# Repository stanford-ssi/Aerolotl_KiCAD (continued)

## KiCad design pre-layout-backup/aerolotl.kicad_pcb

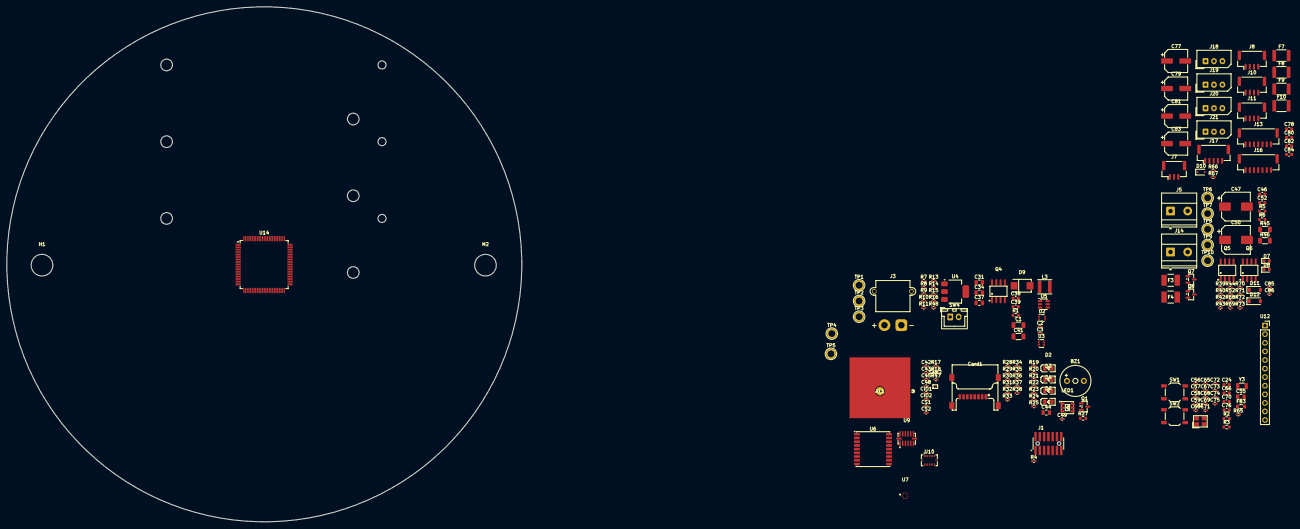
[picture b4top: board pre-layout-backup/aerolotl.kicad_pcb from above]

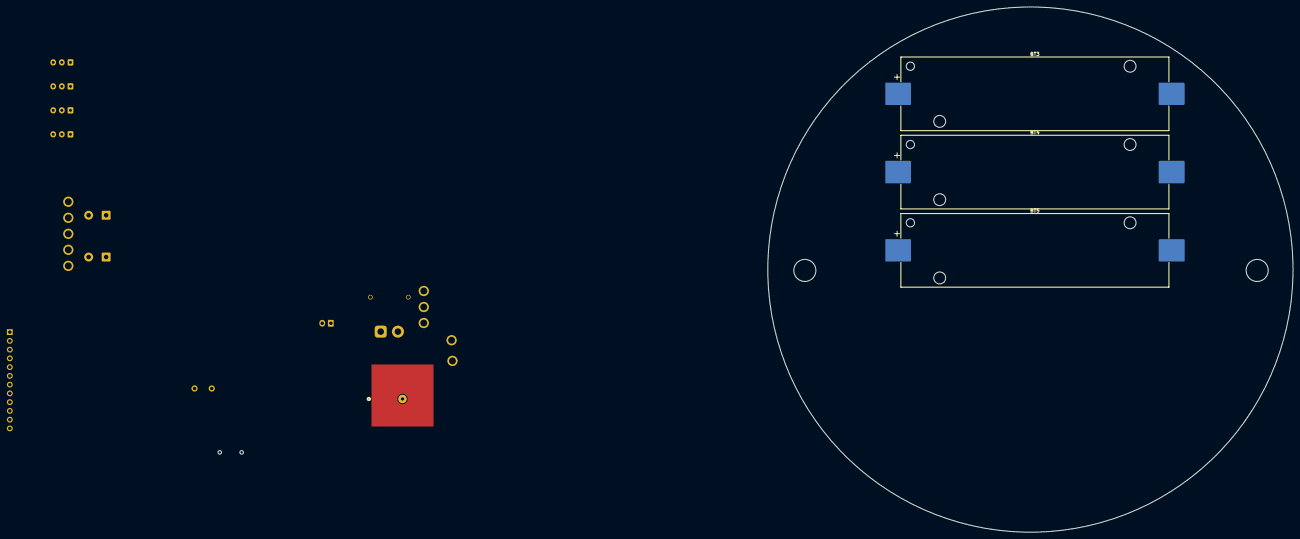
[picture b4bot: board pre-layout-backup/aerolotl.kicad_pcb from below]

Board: 4 copper layers, 152.4 x 152.4 mm, 181 parts (3 on the bottom side), 129 nets, no tracks yet.

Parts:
AE1: GP.1575.18.4.A.02; ANT_GP.1575.18.4.A.02_TAL
BT3, BT4, BT5: Battery_Cell; BatteryHolder_Keystone_1042_1x18650
BZ1: HNB09A03; BUZ-TH_BD9.0-P5.00-D0.6-FD
C1, C41: 100u; C_1206_3216Metric
C2, C3: 1u; C_0402_1005Metric
C24, C38, C39: 100n; C_0603_1608Metric
C31, C34, C44: 22u; C_0805_2012Metric
C37: 4u7; C_0805_2012Metric
C42, C43, C45, C48: 100nF; C_0402_1005Metric
C46, C52: 150n; C_0603_1608Metric
C47, C50: 330u; CP_Elec_8x10
C49, C56, C57, C58, C59, C60, C65, C69, C75, C85, C86: 100n; C_0402_1005Metric
C55: 4.7u; C_0805_2012Metric
C66, C70, C76: 1u; C_0603_1608Metric
C67, C68: 2u2; C_0402_1005Metric
C71, C72, C73, C74: 15p; C_0402_1005Metric
C77, C79, C81, C83: 100u 25V; CP_Elec_6.3x7.7
C78, C80, C82, C84: 100n 50V; C_0603_1608Metric
CIO1: 1u; C_0402_1005Metric
CIO2: 100n; C_0402_1005Metric
CS1: 100n; C_0402_1005Metric
CS2: 1u; C_0402_1005Metric
Card1: TF-102-15_SD_read; TF-SMD_TF-102-15
D2: STM LED; LED0805-R-RD
D3: 3V3 LED; LED0805-R-RD
D4: USB LED; LED0805-R-RD
D6: ARM LED; LED0805-R-RD
D7, D8: LED; LED_0603_1608Metric
D9: SMBJ15A; SMB_L4.6-W3.6-LS5.3-RD
D10: PESD5V0S1BA; D_SOD-323
D11, D12: 1N4148W; D_SOD-123
F3, F4: 1812L150/24MR; FUSE_1812L150&slash_24_LTF
F7, F8, F9, F10: 1812L300/24SLER; Fuse_1812_4532Metric
FB3: 100; L_0805_2012Metric
H1, H2: MountingHole; MountingHole_6.4mm_M6_ISO7380
J1: FTSH-107-STDC14; STDC14_SAMTEC_FTSH-107-01-L-DV-K-A
J3: Pin Switch Conn; AMASS_XT30PW-M_1x02_P2.50mm_Horizontal
J5, J14: Screw_Terminal_01x02; TerminalBlock_Phoenix_MKDS-1,5-2-5.08_1x02_P5.08mm_Horizont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
J7: SPARE_ADC1; JST_GH_BM03B-GHS-TBT_1x03-1MP_P1.25mm_Vertical
J8: Conn_01x04_Pin; JST_GH_BM04B-GHS-TBT_1x04-1MP_P1.25mm_Vertical
J10: USART3; JST_GH_BM04B-GHS-TBT_1x04-1MP_P1.25mm_Vertical
J11: UART8; JST_GH_BM04B-GHS-TBT_1x04-1MP_P1.25mm_Vertical
J13: GPIO_PE2-PE6; JST_GH_BM07B-GHS-TBT_1x07-1MP_P1.25mm_Vertical
J16: GPIO_PE7-PE11; JST_GH_BM07B-GHS-TBT_1x07-1MP_P1.25mm_Vertical
J17: Conn_01x05_Pin; JST_GH_BM05B-GHS-TBT_1x05-1MP_P1.25mm_Vertical
J18: SERVO1; Molex_SPOX_5267-03A_1x03_P2.50mm_Vertical
J19: SERVO2; Molex_SPOX_5267-03A_1x03_P2.50mm_Vertical
J20: SREVO3; Molex_SPOX_5267-03A_1x03_P2.50mm_Vertical
J21: SERVO4; Molex_SPOX_5267-03A_1x03_P2.50mm_Vertical
L3: 4u7; L_Sunlord_SWPA4030S
LED1: RS-3535MWAR-2JYJY-J; LED-SMD_RS-3535MWAR-2JYJY-J
Q1, Q7, Q8: AO3400A; SOT-23
Q4: AO4407A; SOIC-8_L4.9-W3.9-P1.27-LS6.0-BL
Q5, Q6: FDS6673BZ_C467780; SOIC-8_L4.9-W3.9-P1.27-LS6.0-BL
R1: 0R; R_0603_1608Metric
R2, R3: 10k; R_0603_1608Metric
R4, R39, R52: 100; R_0402_1005Metric
R5, R6, R27: 3k3; R_0603_1608Metric
R7, R13, R34, R35, R36, R37, R38, R68, R70, R71, R73: 10k; R_0402_1005Metric
R8, R9: 5k1; R_0402_1005Metric
R10: 9k53; R_0402_1005Metric
R11: 5k; R_0402_1005Metric
R14: 3k3; R_0402_1005Metric
R15, R48: 100k; R_0402_1005Metric
R16: 22k1; R_0402_1005Metric
R17, R18, R28, R29, R30, R31, R32, R33, R47: 10; R_0402_1005Metric
R19, R20, R21, R40, R43, R67: 330; R_0402_1005Metric
R22: 3.3k; R_0402_1005Metric
R23, R24: 470; R_0402_1005Metric
R25: 910; R_0402_1005Metric
R42, R44: 8.2k; R_0402_1005Metric
R45, R46: 1k; R_1206_3216Metric
R65: 47; R_0402_1005Metric
R66: 4.7k; R_0402_1005Metric
R69, R72: 33k; R_0402_1005Metric
SAW2: B39162B4300F210; FILTER-SMD_5P-L1.4-W1.1_RSFPXXXXD
SW1: SW_Push; SW_SPST_TL3342
SW2: SW_SPST; SW_SPST_TL3342
SW4: SW_SPST; JST_XH_B2B-XH-A_1x02_P2.50mm_Vertical
TP1: +BATT; TestPoint_Plated_Hole_D2.0mm
TP2: +12V; TestPoint_Plated_Hole_D2.0mm
TP3: +3V3; TestPoint_Plated_Hole_D2.0mm
TP4: VOLT_SENSE; TestPoint_Plated_Hole_D2.0mm
TP5: GND; TestPoint_Plated_Hole_D2.0mm
TP6: +12V_ARM; TestPoint_Plated_Hole_D2.0mm
TP7: SENSE_I0; TestPoint_Plated_Hole_D2.0mm
TP8: SENSE_I1; TestPoint_Plated_Hole_D2.0mm
TP9: IGNITE_0; TestPoint_Plated_Hole_D2.0mm
TP10: IGNITE_1; TestPoint_Plated_Hole_D2.0mm
U2: USBLC6-2P6; SOT-666
U3: TPS2116DRL; SOT-583-8
U4: AMS1117-3.3; SOT-223-3_TabPin2
U5: LMR51430XFDDCR; SOT-23-6
U6: MAX-M10S; ublox_MAX
U7: BMP581; LGA-10_L2.0-W2.0-P0.50-TL_BMP581
U9: ADXL375BCCZ-RL7; ADXL375_LGA-14_L5.0-W3.0-P0.80-BL
U10: BMI088; Bosch_LGA-16_4.5x3mm_P0.5mm_LayoutBorder7x1y_ClockwisePinNu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
U12: Airlift; PinSocket_1x12_P2.54mm_Vertical
U14: STM32H723VGTx; LQFP-100_14x14mm_P0.5mm
X1: X322525MOB4SI; CRYSTAL-SMD_4P-L3.2-W2.5-BL
Y3: 32k768; Crystal_SMD_3215-2Pin_3.2x1.5mm

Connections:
+3.3VA: C69.1, C70.1, FB3.1, R65.1, U14.21 (VDDA)
+3V3: BZ1.1 (+), C1.1, C44.1, C45.1, C48.1, C49.1, C55.1, C56.1, C57.1, C58.1, C59.1, C60.1, C75.1, C76.1, CIO1.1, CIO2.1, CS1.1, Card1.4 (VDD), D3.1 (+), D11.2 (A), D12.2 (A), FB3.2, J1.03, J7.2, J8.4, J10.4, J11.4, J13.7, J16.7, J17.5, LED1.4 (A), LED1.5 (A), LED1.6 (A), R2.1, R7.1, R17.1, R18.1, R34.1, R35.1, R36.1, R37.1, R38.1, R47.1, R66.1, SW2.2 (B), TP3.1 (1_1), U3.2 (VOUT), U3.7 (VOUT), U6.6 (V_BCKP), U6.7 (VCC_IO), U6.8 (VCC), U9.1 (VDDI/O), U9.3 (RESERVED), U9.6 (VS), U10.3 (VDD), U10.11 (VDDIO), U12.1 (VIN), U14.6 (VBAT), U14.11 (VDD), U14.27 (VDD), U14.50 (VDD), U14.75 (VDD), U14.100 (VDD)
+3V3_BAT: C2.1, C41.1, L3.2, R10.1, R15.1, U3.3 (VIN1), U3.5 (MODE)
+5V: D4.1 (+), R1.1
+12V: C37.1, C38.1, D9.1, F7.1, F8.1, F9.1, F10.1, Q4.1 (S), Q4.2 (S), Q4.3 (S), R13.1, SW4.1 (A), TP2.1 (1_1), U5.3 (VIN), U5.5 (EN)
+12V_ARM: C46.1, C47.1, C50.1, C52.1, D6.1 (+), Q5.1 (S), Q5.2 (S), Q5.3 (S), Q6.1 (S), Q6.2 (S), Q6.3 (S), R5.2, R6.2, R45.1, R46.1, SW4.2 (B), TP6.1 (1_1)
+BATT: J3.1, Q4.5 (D), Q4.6 (D), Q4.7 (D), Q4.8 (D), TP1.1 (1_1)
/Debugger/GNDDetect: J1.11, R4.2
/Debugger/T_NRST: C24.1, J1.12, R2.2, SW1.2, U14.14 (NRST)
/Debugger/T_SWCLK: J1.06, U14.76 (DEBUG_JTCK-SWCLK)
/Debugger/T_SWDIO: J1.04, U14.72 (DEBUG_JTMS-SWDIO)
/Debugger/T_SWO: J1.08, U14.89 (DEBUG_JTDO-SWO)
/Debugger/T_VCP_RX: J1.14, U14.68 (USART1_TX)
/Debugger/T_VCP_TX: J1.13, U14.69 (USART1_RX)
/External/GPIO.PE2: J13.2, U14.1 (PE2)
/External/GPIO.PE3: J13.3, U14.2 (PE3)
/External/GPIO.PE4: J13.4, U14.3 (PE4)
/External/GPIO.PE5: J13.5, U14.4 (PE5)
/External/GPIO.PE6: J13.6, U14.5 (PE6)
/External/GPIO.PE7: J16.2, U14.37 (PE7)
/External/GPIO.PE8: J16.3, U14.38 (PE8)
/External/GPIO.PE9: J16.4, U14.39 (PE9)
/External/GPIO.PE10: J16.5, U14.40 (PE10)
/External/GPIO.PE11: J16.6, U14.41 (PE11)
/External/I2C4.SCL: J8.2, U14.59 (PD12)
/External/I2C4.SDA: J8.3, U14.60 (PD13)
/External/SERVO_BUS: D10.2 (A2), J18.3, J19.3, J20.3, J21.3, R67.2
/External/SERVO_UART: R66.2, R67.1, U14.82 (UART4_TX)
/External/SPARE_ADC1: J7.1, U14.28 (PA4)
/External/SPI4.MISO: J17.3, U14.43 (SPI4_MISO)
/External/SPI4.MOSI: J17.2, U14.44 (SPI4_MOSI)
/External/SPI4.SCK: J17.4, U14.42 (SPI4_SCK)
/External/UART8_TARGET_RX: J11.2, U14.97 (UART8_RX)
/External/UART8_TARGET_TX: J11.3, U14.98 (UART8_TX)
/External/USART3_TARGET_RX: J10.2, U14.56 (USART3_RX)
/External/USART3_TARGET_TX: J10.3, U14.55 (USART3_TX)
/Igniter/IGN0: D8.2 (A), Q7.1 (G), R42.1, TP9.1 (1_1), U14.61 (PD14)
/Igniter/IGN0_HS: J14.1, Q5.5 (D), Q5.6 (D), Q5.7 (D), Q5.8 (D), R68.2, R69.1
/Igniter/IGN1: D7.2 (A), Q8.1 (G), R44.1, TP10.1 (1_1), U14.62 (PD15)
/Igniter/IGN1_HS: J5.1, Q6.5 (D), Q6.6 (D), Q6.7 (D), Q6.8 (D), R71.2, R72.1
/Igniter/SENSE_I0: C85.1, R69.2, R70.1, TP7.1 (1_1), U14.22 (PA0)
/Igniter/SENSE_I1: C86.1, R72.2, R73.1, TP8.1 (1_1), U14.23 (PA1)
/Indicators/BUZZER: Q1.1 (G), R22.1, U14.67 (TIM1_CH1)
/Indicators/LED: D2.1 (+), U14.77 (PA15(JTDI))
/Indicators/LED.B: R21.2, U14.63 (PC6)
/Indicators/LED.G: R20.2, U14.33 (PC5)
/Indicators/LED.R: R19.2, U14.32 (PC4)
/MCU/BOOT0: R3.1, SW2.1 (A), U14.94 (BOOT0)
/MCU/GPS_RST: U6.9 (~RESET), U14.91 (PB5)
/MCU/HS_OSC_A: C73.1, U14.12 (RCC_OSC_IN), X1.1 (OSC1)
/MCU/HS_OSC_B: C74.1, U14.13 (RCC_OSC_OUT), X1.3 (OSC2)
/MCU/LS_OSC_A: C72.1, U14.8 (RCC_OSC32_IN), Y3.2
/MCU/LS_OSC_B: C71.1, U14.9 (RCC_OSC32_OUT), Y3.1
/MCU/PWR_STS: R7.2, U3.8 (ST), U14.16 (PC1)
/MCU/SDMMC1.CK: R32.1, U14.80 (SDMMC1_CK)
/MCU/SDMMC1.CMD: R31.1, U14.83 (SDMMC1_CMD)
/MCU/SDMMC1.D0: R33.1, U14.65 (SDMMC1_D0)
/MCU/SDMMC1.D1: R28.1, U14.66 (SDMMC1_D1)
/MCU/SDMMC1.D2: R29.1, U14.78 (SDMMC1_D2)
/MCU/SDMMC1.D3: R30.1, U14.79 (SDMMC1_D3)
/MCU/SPI1.CS_375: U9.7 (~CS), U14.88 (PD7)
/MCU/SPI1.CS_BMP: U7.6 (CSB), U14.86 (PD5)
/MCU/SPI1.CS_IMU_ACC: U10.14 (~CSB1), U14.84 (PD3)
/MCU/SPI1.CS_IMU_GYRO: U10.5 (~CSB2), U14.85 (PD4)
/MCU/SPI1.INT_375: U9.8 (INT1), U14.95 (PB8)
/MCU/SPI1.INT_BMP: U7.7 (INT), U14.96 (PB9)
/MCU/SPI1.INT_IMU_ACC: U10.16 (INT1), U14.45 (PE15)
/MCU/SPI1.INT_IMU_GYRO: U10.12 (INT3), U14.36 (PB2)
/MCU/SPI1.MISO: U7.5 (SDO), U9.12 (SDO/ALTADDRESS), U10.10 (SDO2), U10.15 (SDO1), U14.30 (SPI1_MISO)
/MCU/SPI1.MOSI: U7.4 (SDI), U9.13 (SDA/SDI/SDIO), U10.9 (SDI/SDA), U14.31 (SPI1_MOSI)
/MCU/SPI1.SCK: U7.2 (SCK), U9.14 (SCL/SCLK), U10.8 (SCK/SCL), U14.29 (SPI1_SCK)
/MCU/SPI2.BUSY: U12.8 (BUSY), U14.57 (PD10)
/MCU/SPI2.CS: U12.7 (CS), U14.51 (PB12)
/MCU/SPI2.MISO: U12.5 (MISO), U14.53 (SPI2_MISO)
/MCU/SPI2.MOSI: U12.6 (MOSI), U14.54 (SPI2_MOSI)
/MCU/SPI2.RST: U12.9 (~RST), U14.58 (PD11)
/MCU/SPI2.SCK: U12.4 (SCK), U14.52 (SPI2_SCK)
/MCU/USB_D+: U2.4 (I/O2), U14.71 (USB_OTG_HS_DP)
/MCU/USB_D-: U2.6 (I/O1), U14.70 (USB_OTG_HS_DM)
/Power/P_VBUS: C31.1, R1.2, U2.5 (VBUS), U4.3 (VI)
/Power/USB_3V3: C3.1, C34.1, U3.6 (VIN2), U4.2 (VO)
/Power/VOLT_SENSE: R13.2, R14.1, TP4.1 (1_1), U14.15 (PC0)
/Sensors/GPS_RF_IN: SAW2.4 (OUT), U6.11 (RF_IN)
/Sensors/M10S.RX: U6.3 (RXD), U14.24 (USART2_TX)
/Sensors/M10S.TX: U6.2 (TXD), U14.25 (USART2_RX)
GND: BT5.2 (-), C1.2, C2.2, C3.2, C24.2, C31.2, C34.2, C37.2, C38.2, C41.2, C42.2, C43.2, C44.2, C45.2, C47.2, C48.2, C49.2, C50.2, C55.2, C56.2, C57.2, C58.2, C59.2, C60.2, C65.2, C66.2, C67.2, C68.2, C69.2, C70.2, C71.2, C72.2, C73.2, C74.2, C75.2, C76.2, C77.2, C78.2, C79.2, C80.2, C81.2, C82.2, C83.2, C84.2, C85.2, C86.2, CIO1.2, CIO2.2, CS1.2, CS2.2, Card1.6 (VSS), Card1.9 (SHELL), Card1.10 (SHELL), Card1.11 (SHELL), Card1.12 (SHELL), D9.2, D10.1 (A1), F3.1, F4.1, J1.05, J1.07, J7.3, J8.1, J10.1, J11.1, J13.1, J16.1, J17.1, J18.1, J19.1, J20.1, J21.1, Q1.2 (S), Q7.2 (S), Q8.2 (S), R3.2, R4.1, R5.1, R6.1, R8.2, R9.2, R11.2, R14.2, R16.2, R22.2, R23.2, R24.2, R25.2, R27.2, R40.2, R42.2, R43.2, R44.2, R48.2, R70.2, R73.2, SAW2.2 (GND), SAW2.3 (GND), SAW2.5 (GND), SW1.1, TP5.1 (1_1), U2.2 (GND), U3.1 (GND), U4.1 (GND), U5.1 (GND), U6.1 (GND), U6.10 (GND), U6.12 (GND), U7.3 (VSS), U7.8 (VSS), U7.9 (VSS), U9.2 (GND), U9.4 (GND), U9.5 (GND), U9.11 (RESERVED), U10.2 (GNDA), U10.4 (GNDA), U10.6 (GNDIO), U10.7 (PS), U12.3 (GND), U14.10 (VSS), U14.19 (VSSA), U14.26 (VSS), U14.49 (VSS), U14.74 (VSS), U14.99 (VSS), X1.2 (GND), X1.4 (GND)
unnamed: BT3.1 (+), J3.2
unnamed: BT3.2 (-), BT4.1 (+)
unnamed: BT4.2 (-), BT5.1 (+)
unnamed: BZ1.2 (-), Q1.3 (D)
unnamed: C67.1, U14.48 (VCAP)
unnamed: C68.1, U14.73 (VCAP)
unnamed: Card1.2 (CD/DAT3), R30.2, R37.2
unnamed: Card1.5 (CLK), R32.2
unnamed: Card1.3 (CMD), R31.2, R36.2
unnamed: Card1.7 (DAT0), R33.2, R35.2
unnamed: Card1.8 (DAT1), R28.2, R34.2
unnamed: Card1.1 (DAT2), R29.2, R38.2
unnamed: D2.2 (-), R23.1
unnamed: D3.2 (-), R24.1
unnamed: D4.2 (-), R25.1
unnamed: D6.2 (-), R27.1
unnamed: D7.1 (K), R43.1
unnamed: D8.1 (K), R40.1
unnamed: D11.1 (K), R68.1
unnamed: D12.1 (K), R71.1
unnamed: F3.2, J5.2
unnamed: F4.2, J14.2
unnamed: C77.1, C78.1, F7.2, J18.2
unnamed: C79.1, C80.1, F8.2, J19.2
unnamed: C81.1, C82.1, F9.2, J20.2
unnamed: C83.1, C84.1, F10.2, J21.2
unnamed: LED1.1 (K), R21.1
unnamed: LED1.2 (K), R20.1
unnamed: LED1.3 (K), R19.1
unnamed: Q4.4 (G), R48.1
unnamed: C46.2, Q5.4 (G), R39.1, R46.2
unnamed: C52.2, Q6.4 (G), R45.2, R52.1
unnamed: Q7.3 (D), R39.2
unnamed: Q8.3 (D), R52.2
unnamed: AE1.1 (1_1), SAW2.1 (IN)
unnamed: CS2.1, R47.2
unnamed: R10.2, R11.1, U3.4 (PR1)
unnamed: C39.1, U5.6 (CB)
unnamed: R15.2, R16.1, U5.4 (FB)
unnamed: C39.2, L3.1, U5.2 (SW)
unnamed: C43.1, R18.2, U7.10 (VDD)
unnamed: C42.1, R17.2, U7.1 (VDDIO)
unnamed: C65.1, C66.1, R65.2, U14.20 (VREF+)

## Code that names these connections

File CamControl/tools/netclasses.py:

"""Write CamControl net classes + patterns into camcontrol.kicad_pro (KiCad must be closed)."""
import json, sys, os
PRO = sys.argv[1] if len(sys.argv) > 1 else "camcontrol.kicad_pro"
# name, track, clearance, via_d, via_drill, priority (lower = wins)
CLASSES = [
    ("Pyro",   1.00, 0.40, 0.80, 0.40, 0),
    ("Power",  1.00, 0.20, 0.80, 0.40, 1),
    ("Signal", 0.30, 0.20, 0.60, 0.30, 2),
]
PATTERNS = {
    # carry real current from the 2S pack
    "Power": ["*/VBAT+", "*/VF", "*/VSW", "*/VIN", "*/+5V", "*/SW", "GND", "Net-(BT1--)"],
    # carry each altimeter's e-match firing current (~10 A for a few ms)
    "Pyro": ["*/COTS_BAT+", "*/COTS_BAT-", "*/COTS_SW", "*/SRAD_BAT+", "*/SRAD_BAT-", "*/SRAD_SW"],
    "Signal": ["*/ESP_TX2", "*/ESP_RX2", "*/CAM_RX", "*/CAM_TX", "*/LED_GPIO", "*/LED_A", "*/VBAT_SENSE", "*/FB", "*/CBOOT"],
}
p = json.load(open(PRO))
ns = p["net_settings"]
default = next(c for c in ns["classes"] if c["name"] == "Default")
default.update({"track_width": 0.30, "clearance": 0.20, "via_diameter": 0.60, "via_drill": 0.30})
out = [default]
for name, tw, cl, vd, vr, pri in CLASSES:
    c = dict(default)
    c.update({"name": name, "track_width": tw, "clearance": cl, "via_diameter": vd, "via_drill": vr, "priority": pri})
    out.append(c)
ns["classes"] = out
ns["netclass_patterns"] = [{"netclass": k, "pattern": pat} for k, pats in PATTERNS.items() for pat in pats]
ds = p["board"]["design_settings"]
ds["track_widths"] = [0.0, 0.25, 0.3, 0.5, 1.0, 1.5, 2.0]
ds["via_dimensions"] = [{"diameter": 0.0, "drill": 0.0}, {"diameter": 0.6, "drill": 0.3}, {"diameter": 0.8, "drill": 0.4}]
json.dump(p, open(PRO, "w"), indent=2)
print("net classes:", [(c["name"], c["track_width"], c["clearance"], c["via_diameter"], c["via_drill"], c["priority"]) for c in out])
print("patterns:", len(ns["netclass_patterns"]))

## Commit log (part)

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2026-02-20 Initial commit for kicad collaboration
2026-02-21 added load capacitors to oscillator
2026-02-21 Add voltage step down 12V to 3V3
2026-02-21 Added voltage step down form 12V to 3V3
2026-02-21 todo list
2026-02-21 Added todo list
2026-02-21 added usbc receptacle back
2026-02-21 made stemma qt footprint and symbol and 3d model
2026-02-21 changed stemma qt connector name
2026-02-22 Modified schematics for IMUs
2026-02-22 added adxl375
2026-02-22 forgot to commit symbol for adxl375, did it now
2026-02-22 Power Schematic semi-finalized
2026-02-22 Added indicator circuits
2026-02-22 Began external circuitry
2026-02-22 Current progress on externals
2026-02-22 Commit current state before applying gitignore
2026-02-22 Untrack junk KiCad files and enforce .gitignore
2026-02-22 Refactor repository: consolidate custom libraries, move hierarchical sheets, and clean up root directory
2026-02-23 fixed adxl pins, added hierarchical bus connections
2026-02-23 added current rush limiting resistors to bmp581
2026-02-23 Untrack kicad auto save file, hopefully caleb won't have issues pulling anymore lol
2026-02-23 added SparkFunM9N breakout board footprint
2026-02-23 Added NEOM9N breakout symbol
2026-02-23 Wired NEOM9N breakout
2026-02-23 Fixed up power, added remaining to do
2026-02-24 polished up circuit, added new 16.8V to 7.4V step down circuit components
2026-02-24 Made 7.4V stepdown circuit in power sheet
2026-02-24 checked up w Lawton
2026-02-24 second push
2026-02-24 Added pinouts for I2C
2026-02-24 Deleted I2C3
2026-02-24 Routed all external I2C connectors
2026-02-24 connected pwm, spare uarts, i2cs, etc.
2026-02-24 removed fd can
2026-02-25 added spi
2026-02-25 led pwm
2026-02-25 added Capacitor values for sensors
2026-02-25 assigned gpio pin to led (pg6)
2026-02-25 added gpio connections in root, UART8, ADC2
2026-02-25 final pwm channels added
2026-02-25 final rev1
2026-02-25 Rev1 schematic done
2026-02-25 Cleared all ERC errors
2026-02-25 moving onto pcb layout and footprinting
2026-02-26 Cleared ALL ERC warnings
2026-02-26 added capacitor values to sensors
2026-02-27 some footprints assigned
2026-02-27 letter size schematic pages formatted
